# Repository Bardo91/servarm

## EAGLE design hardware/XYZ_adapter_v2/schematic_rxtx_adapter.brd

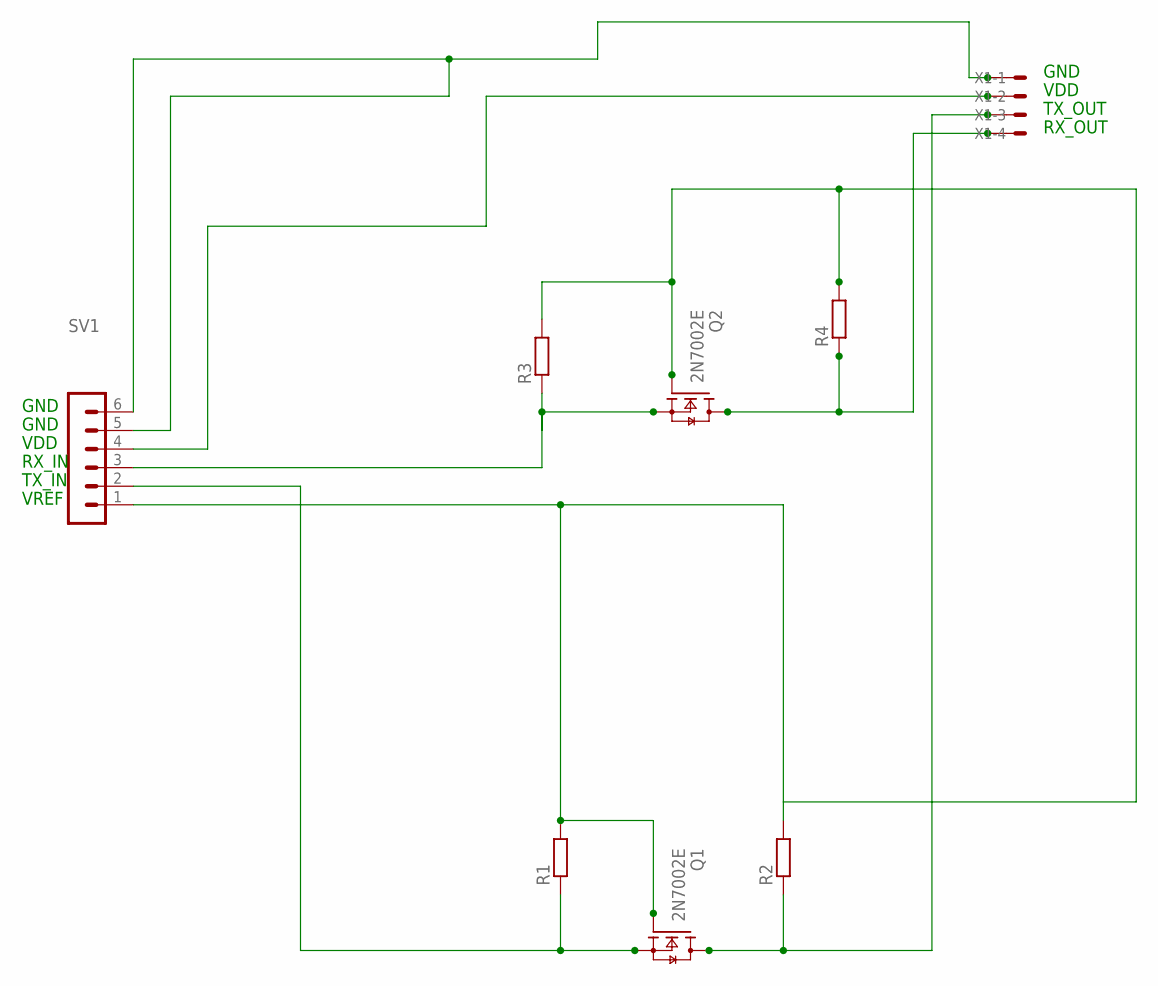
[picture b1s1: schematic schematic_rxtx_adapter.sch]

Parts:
Q1, Q2: 2N7002E; SOT23
R1, R2: R-EU_0207/12; 0207/12
R3, R4: R-EU_0207/10; 0207/10
SV1: MA06-1
X1: L04P

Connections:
GND: SV1.5, SV1.6, X1.1
RX_IN: Q2.2 (S), R3.1, SV1.3
RX_OUT: Q2.3 (D), R4.1, X1.4
TX_IN: Q1.2 (S), R1.1, SV1.2
TX_OUT: Q1.3 (D), R2.1, X1.3
VDD: SV1.4, X1.2
VREF: Q1.1 (G), Q2.1 (G), R1.2, R2.2, R3.2, R4.2, SV1.1

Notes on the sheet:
GND
VDD
VREF
RX_IN
TX_IN
TX_OUT
RX_OUT

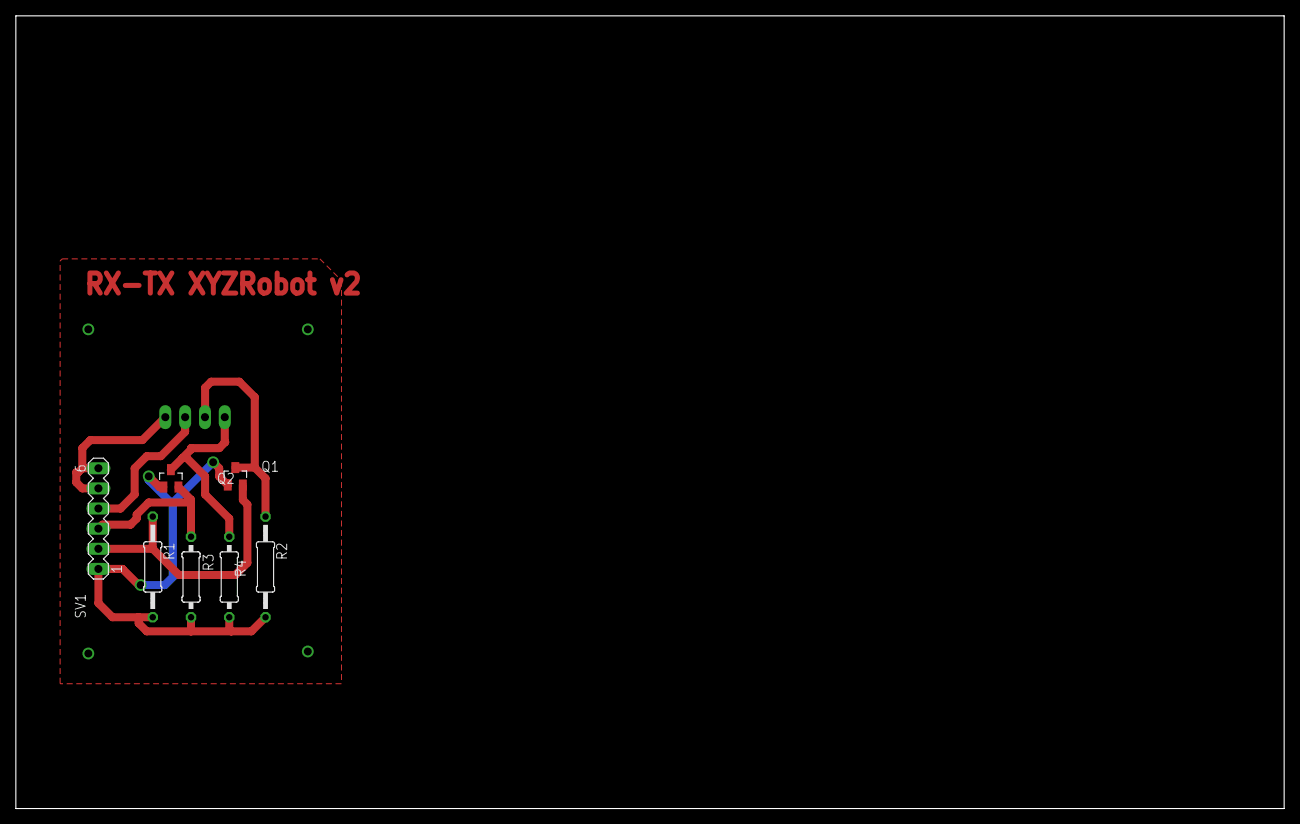
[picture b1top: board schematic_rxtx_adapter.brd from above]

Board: 2 copper layers, 160.0 x 100.0 mm, 8 parts (1 on the bottom side), 7 nets.

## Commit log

2018-10-15 Init repo
2018-10-17 added circuits rx_tx adapter
2018-10-17 Updated xyz_adapter_v2
2018-10-18 Updated cad models
